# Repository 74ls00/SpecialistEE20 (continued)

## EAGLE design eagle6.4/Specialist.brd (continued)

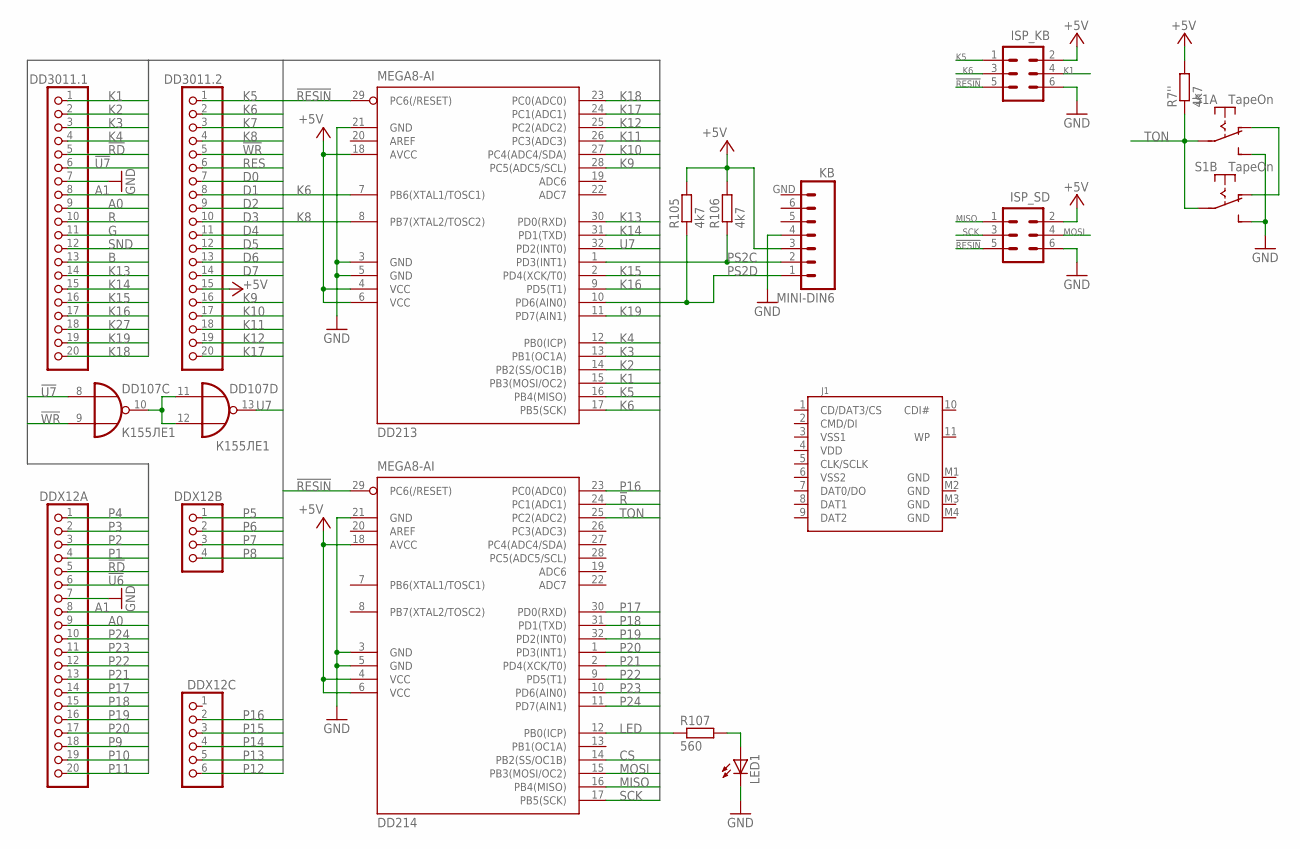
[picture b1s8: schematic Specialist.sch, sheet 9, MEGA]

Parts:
DD107: К155ЛЕ1; DIL14
DD213, DD214: MEGA8-AI; TQFP32-08
DD3011.1, DD3011.2: PINHD-1X20; 1X20
DDX12A: PINHD-1X20; 1X20
DDX12B: PINHD-1X4; 1X04
DDX12C: PINHD-1X6; 1X06
ISP_KB: MA03-2
ISP_SD: MA03-2
J1: SDCARD; SDCMF-10915W010
KB: MINI-DIN6
LED1: LED5MM
R7'', R105, R106: 4k7; M0805
R107: 560; M0805
S1: TapeOn; SWITCH9X4

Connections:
!R: DD214.24 (PC1(ADC1))
!RD: DD3011.1.5, DDX12A.5; also elsewhere on the board
!RESIN: DD213.29 (PC6(/RESET)), DD214.29 (PC6(/RESET)), ISP_KB.5, ISP_SD.5
!U6: DDX12A.6; also elsewhere on the board
!U7: DD107.8 (I0), DD3011.1.6; also elsewhere on the board
!WR: DD107.9 (I1), DD3011.2.5; also elsewhere on the board
+5V: DD213.4 (VCC), DD213.6 (VCC), DD213.18 (AVCC), DD214.4 (VCC), DD214.6 (VCC), DD214.18 (AVCC), DD3011.2.15, ISP_KB.2, ISP_SD.2, KB.3, R7''.2, R105.2, R106.2; also elsewhere on the board
A0: DD3011.1.9, DDX12A.9; also elsewhere on the board
A1: DD3011.1.8, DDX12A.8; also elsewhere on the board
B: DD3011.1.13; also elsewhere on the board
CS: DD214.14 (PB2(SS/OC1B))
D0: DD3011.2.7; also elsewhere on the board
D1: DD3011.2.8; also elsewhere on the board
D2: DD3011.2.9; also elsewhere on the board
D3: DD3011.2.10; also elsewhere on the board
D4: DD3011.2.11; also elsewhere on the board
D5: DD3011.2.12; also elsewhere on the board
D6: DD3011.2.13; also elsewhere on the board
D7: DD3011.2.14; also elsewhere on the board
G: DD3011.1.11; also elsewhere on the board
GND: DD213.3 (GND), DD213.5 (GND), DD213.21 (GND), DD214.3 (GND), DD214.5 (GND), DD214.21 (GND), DD3011.1.7, DDX12A.7, ISP_KB.6, ISP_SD.6, J1.M1 (GND), J1.M2 (GND), J1.M3 (GND), J1.M4 (GND), KB.4, LED1.K (C), S1.12 (S), S1.22 (S); also elsewhere on the board
K1: DD213.15 (PB3(MOSI/OC2)), DD3011.1.1, ISP_KB.4; also elsewhere on the board
K2: DD213.14 (PB2(SS/OC1B)), DD3011.1.2; also elsewhere on the board
K3: DD213.13 (PB1(OC1A)), DD3011.1.3; also elsewhere on the board
K4: DD213.12 (PB0(ICP)), DD3011.1.4; also elsewhere on the board
K5: DD213.16 (PB4(MISO)), DD3011.2.1, ISP_KB.1; also elsewhere on the board
K6: DD213.7 (PB6(XTAL1/TOSC1)), DD213.17 (PB5(SCK)), DD3011.2.2, ISP_KB.3; also elsewhere on the board
K7: DD3011.2.3; also elsewhere on the board
K8: DD213.8 (PB7(XTAL2/TOSC2)), DD3011.2.4; also elsewhere on the board
K9: DD213.28 (PC5(ADC5/SCL)), DD3011.2.16; also elsewhere on the board
K10: DD213.27 (PC4(ADC4/SDA)), DD3011.2.17; also elsewhere on the board
K11: DD213.26 (PC3(ADC3)), DD3011.2.18; also elsewhere on the board
K12: DD213.25 (PC2(ADC2)), DD3011.2.19; also elsewhere on the board
K13: DD213.30 (PD0(RXD)), DD3011.1.14; also elsewhere on the board
K14: DD213.31 (PD1(TXD)), DD3011.1.15; also elsewhere on the board
K15: DD213.2 (PD4(XCK/T0)), DD3011.1.16; also elsewhere on the board
K16: DD213.9 (PD5(T1)), DD3011.1.17; also elsewhere on the board
K17: DD213.24 (PC1(ADC1)), DD3011.2.20; also elsewhere on the board
K18: DD213.23 (PC0(ADC0)), DD3011.1.20; also elsewhere on the board
K19: DD213.11 (PD7(AIN1)), DD3011.1.19; also elsewhere on the board
K27: DD3011.1.18; also elsewhere on the board
LED: DD214.12 (PB0(ICP)), R107.1
MISO: DD214.16 (PB4(MISO)), ISP_SD.1
MOSI: DD214.15 (PB3(MOSI/OC2)), ISP_SD.4
unnamed: S1.11 (O), S1.21 (O)
unnamed: DD107.10 (O), DD107.11 (I0), DD107.12 (I1)
unnamed: LED1.A, R107.2
P1: DDX12A.4; also elsewhere on the board
P2: DDX12A.3; also elsewhere on the board
P3: DDX12A.2; also elsewhere on the board
P4: DDX12A.1; also elsewhere on the board
P5: DDX12B.1; also elsewhere on the board
P6: DDX12B.2; also elsewhere on the board
P7: DDX12B.3; also elsewhere on the board
P8: DDX12B.4; also elsewhere on the board
P9: DDX12A.18; also elsewhere on the board
P10: DDX12A.19; also elsewhere on the board
P11: DDX12A.20; also elsewhere on the board
P12: DDX12C.6; also elsewhere on the board
P13: DDX12C.5; also elsewhere on the board
P14: DDX12C.4; also elsewhere on the board
P15: DDX12C.3; also elsewhere on the board
P16: DD214.23 (PC0(ADC0)), DDX12C.2; also elsewhere on the board
P17: DD214.30 (PD0(RXD)), DDX12A.14; also elsewhere on the board
P18: DD214.31 (PD1(TXD)), DDX12A.15; also elsewhere on the board
P19: DD214.32 (PD2(INT0)), DDX12A.16; also elsewhere on the board
P20: DD214.1 (PD3(INT1)), DDX12A.17; also elsewhere on the board
P21: DD214.2 (PD4(XCK/T0)), DDX12A.13; also elsewhere on the board
P22: DD214.9 (PD5(T1)), DDX12A.12; also elsewhere on the board
P23: DD214.10 (PD6(AIN0)), DDX12A.11; also elsewhere on the board
P24: DD214.11 (PD7(AIN1)), DDX12A.10; also elsewhere on the board
PS2C: DD213.1 (PD3(INT1)), KB.2, R106.1
PS2D: DD213.10 (PD6(AIN0)), KB.1, R105.1
R: DD3011.1.10; also elsewhere on the board
RES: DD3011.2.6; also elsewhere on the board
SCK: DD214.17 (PB5(SCK)), ISP_SD.3
SND: DD3011.1.12; also elsewhere on the board
TON: DD214.25 (PC2(ADC2)), R7''.1, S1.10, S1.20
U7: DD107.13 (O), DD213.32 (PD2(INT0))
VDD: J1.4 (VDD)
VSS1: J1.3 (VSS1)
VSS2: J1.6 (VSS2)

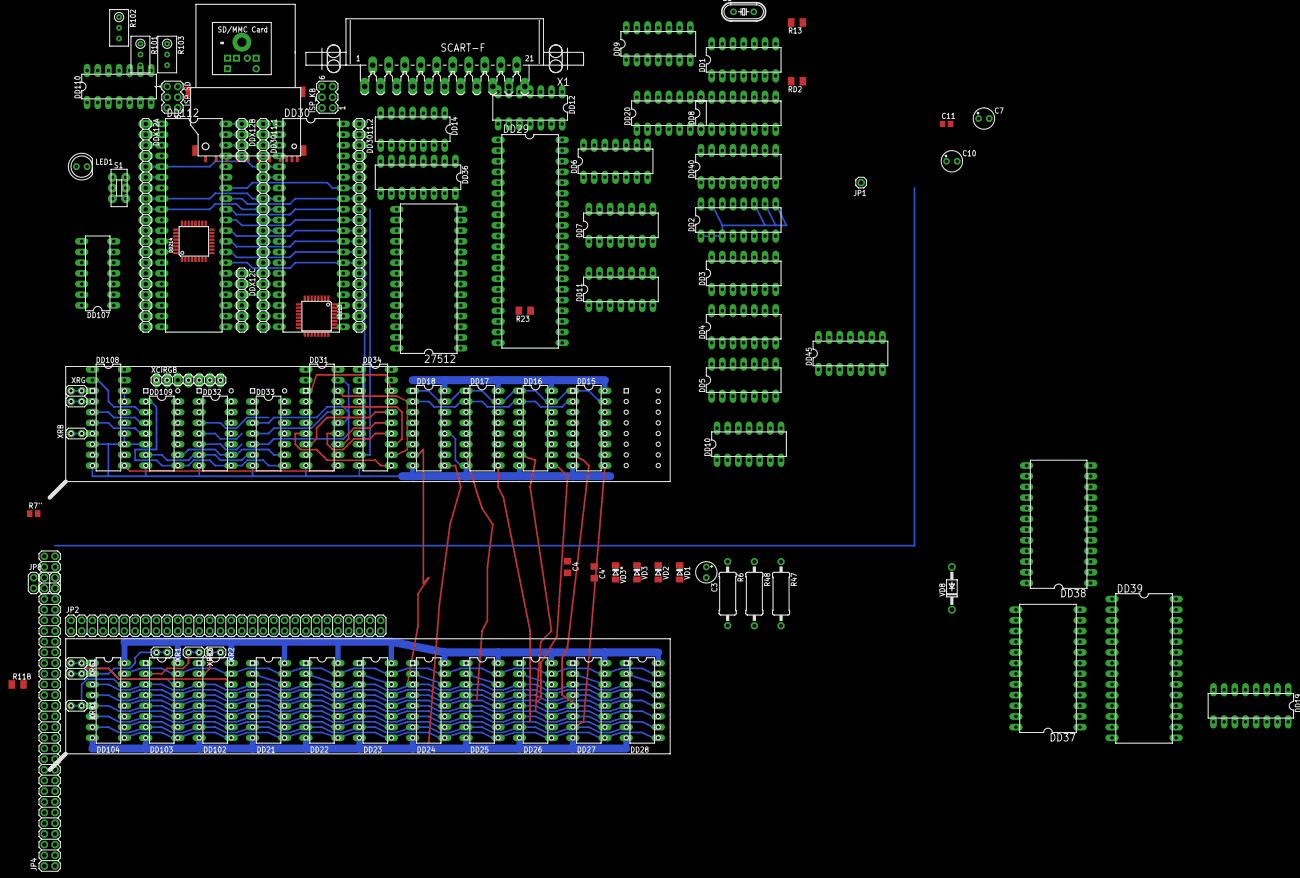
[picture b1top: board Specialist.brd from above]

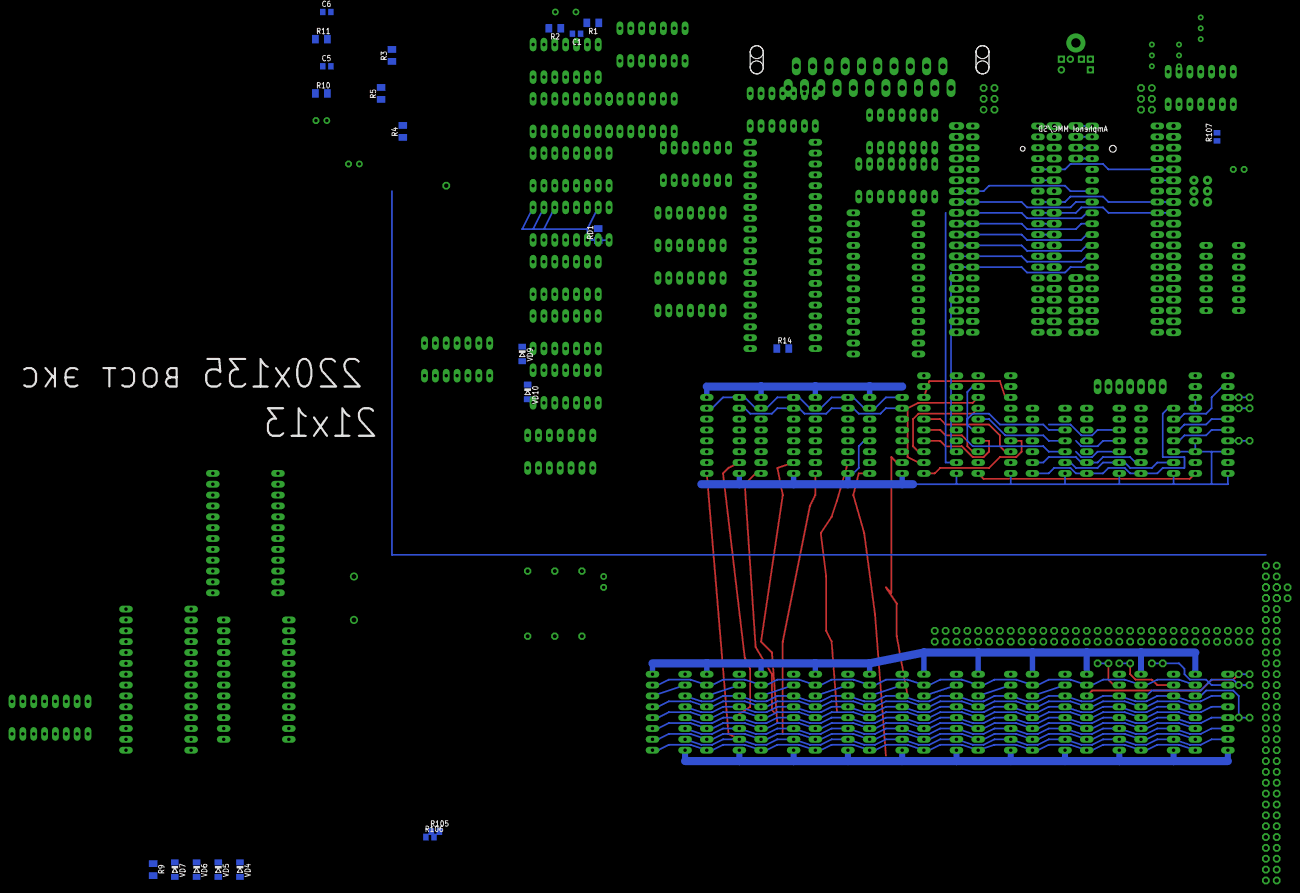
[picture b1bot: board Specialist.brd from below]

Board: 2 copper layers, 122 parts (22 on the bottom side), 213 nets.

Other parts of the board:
U$1, U$3: RAM3+8
U$2: NANOITXPCB
